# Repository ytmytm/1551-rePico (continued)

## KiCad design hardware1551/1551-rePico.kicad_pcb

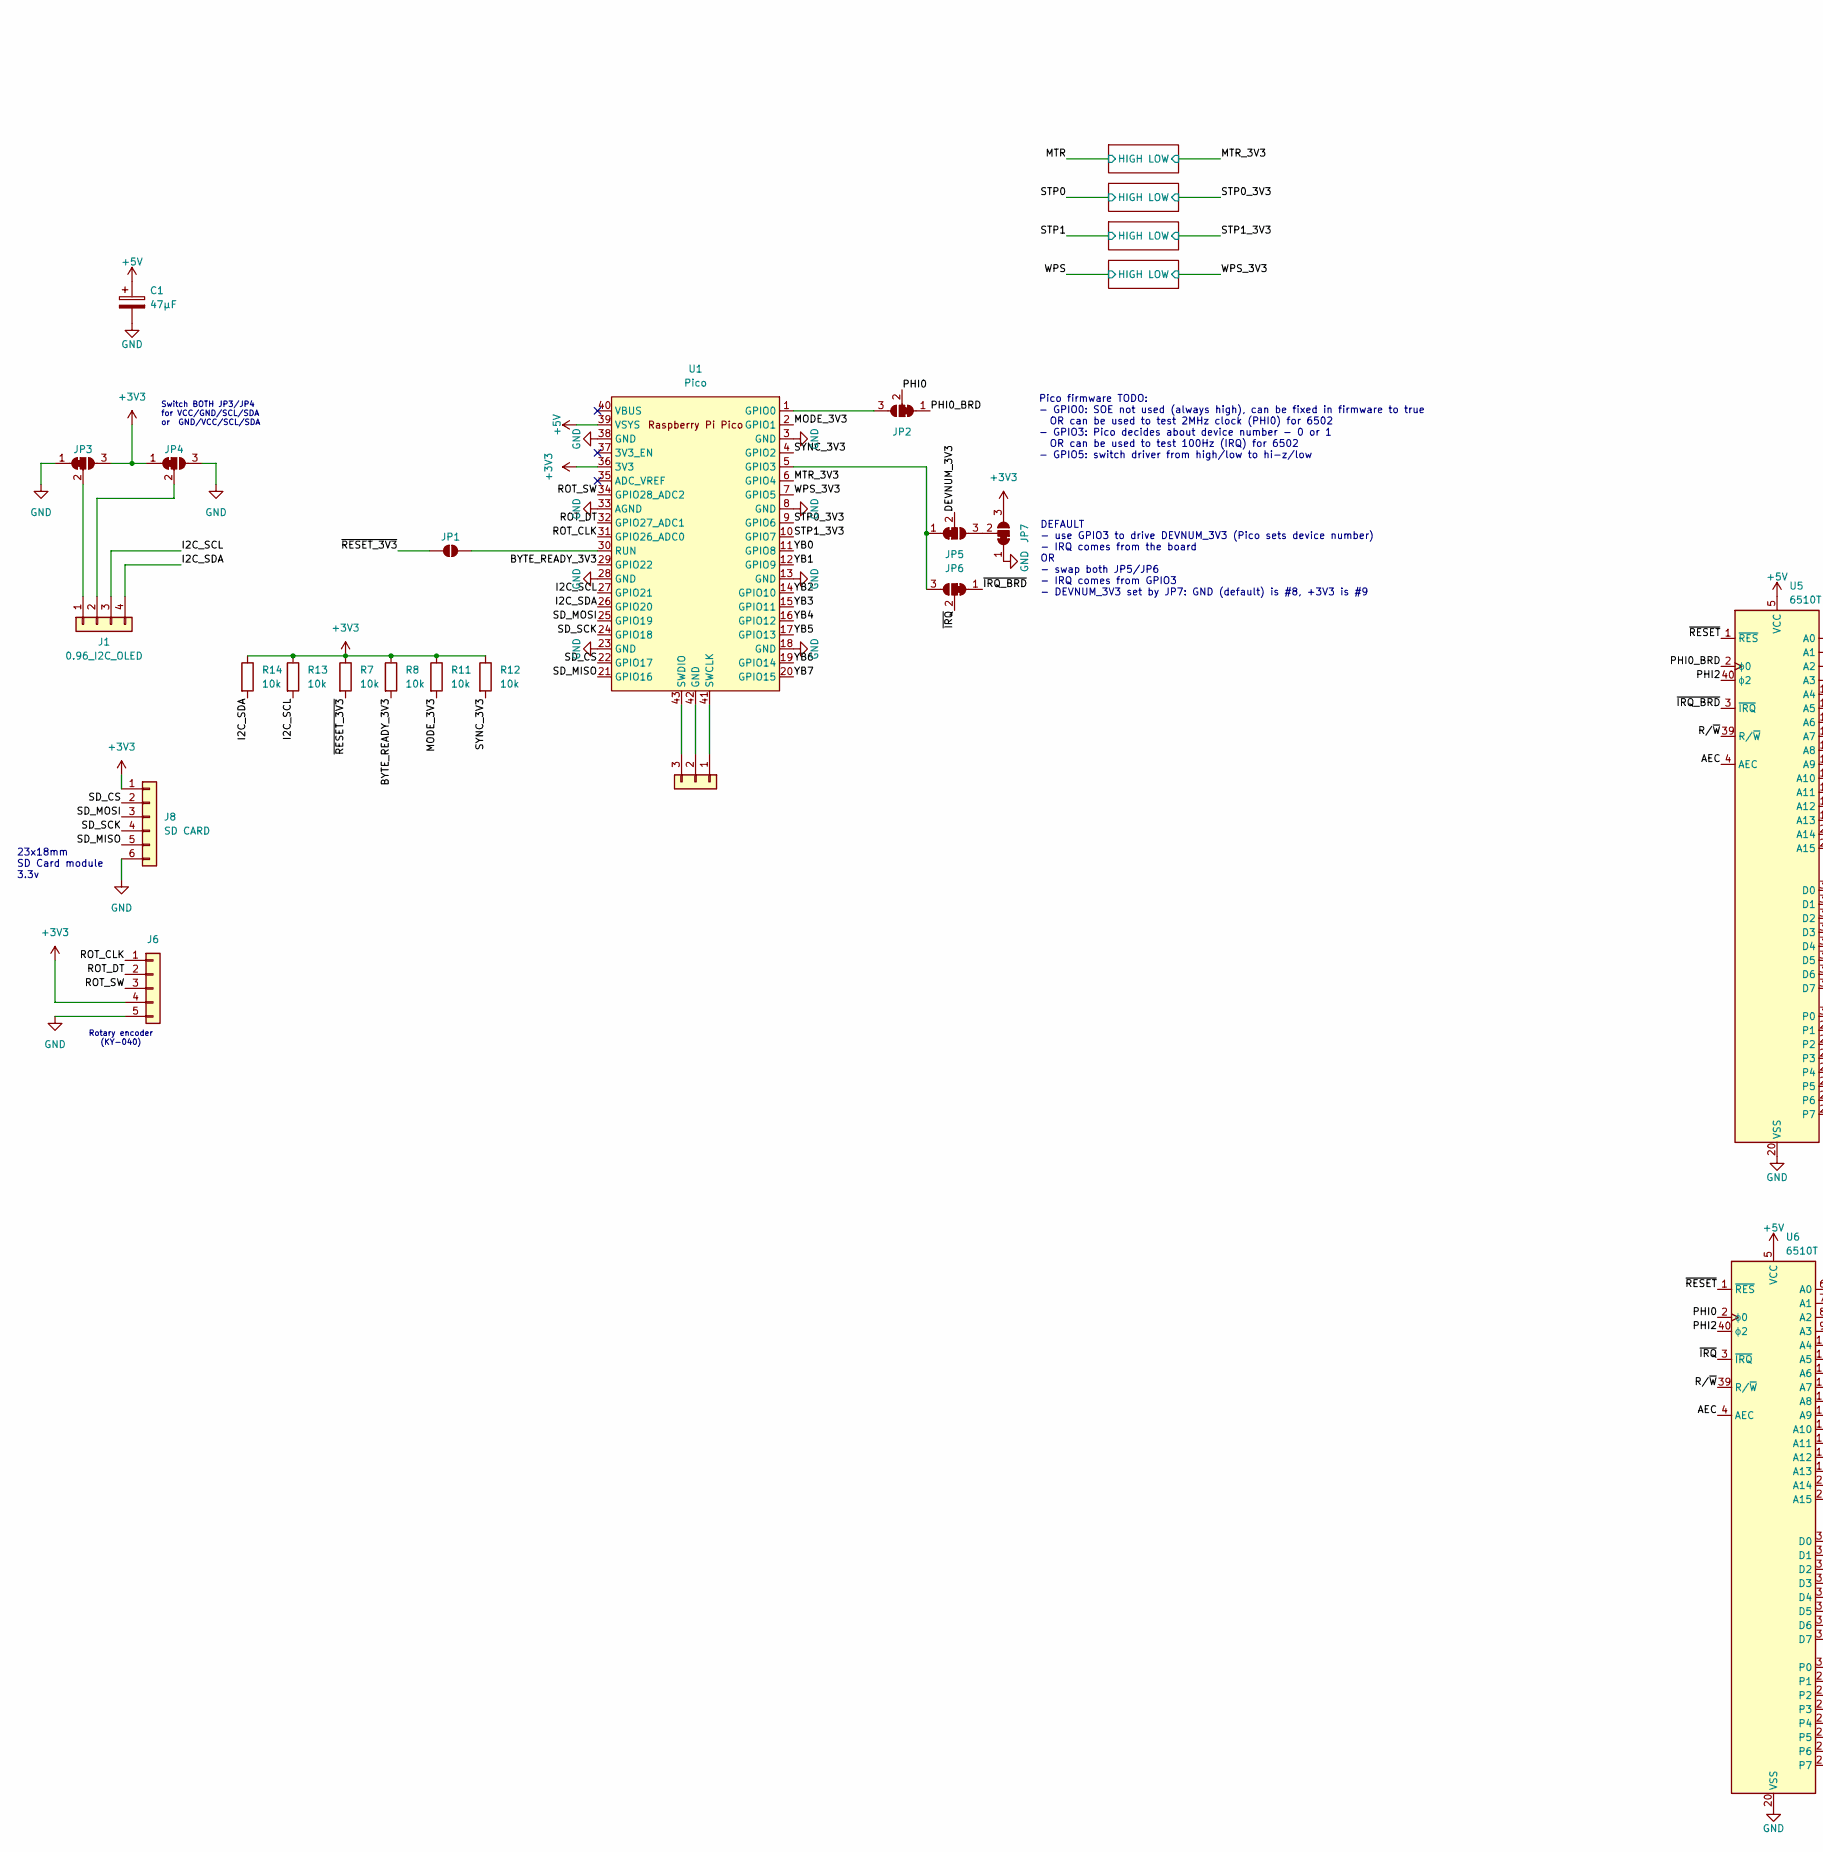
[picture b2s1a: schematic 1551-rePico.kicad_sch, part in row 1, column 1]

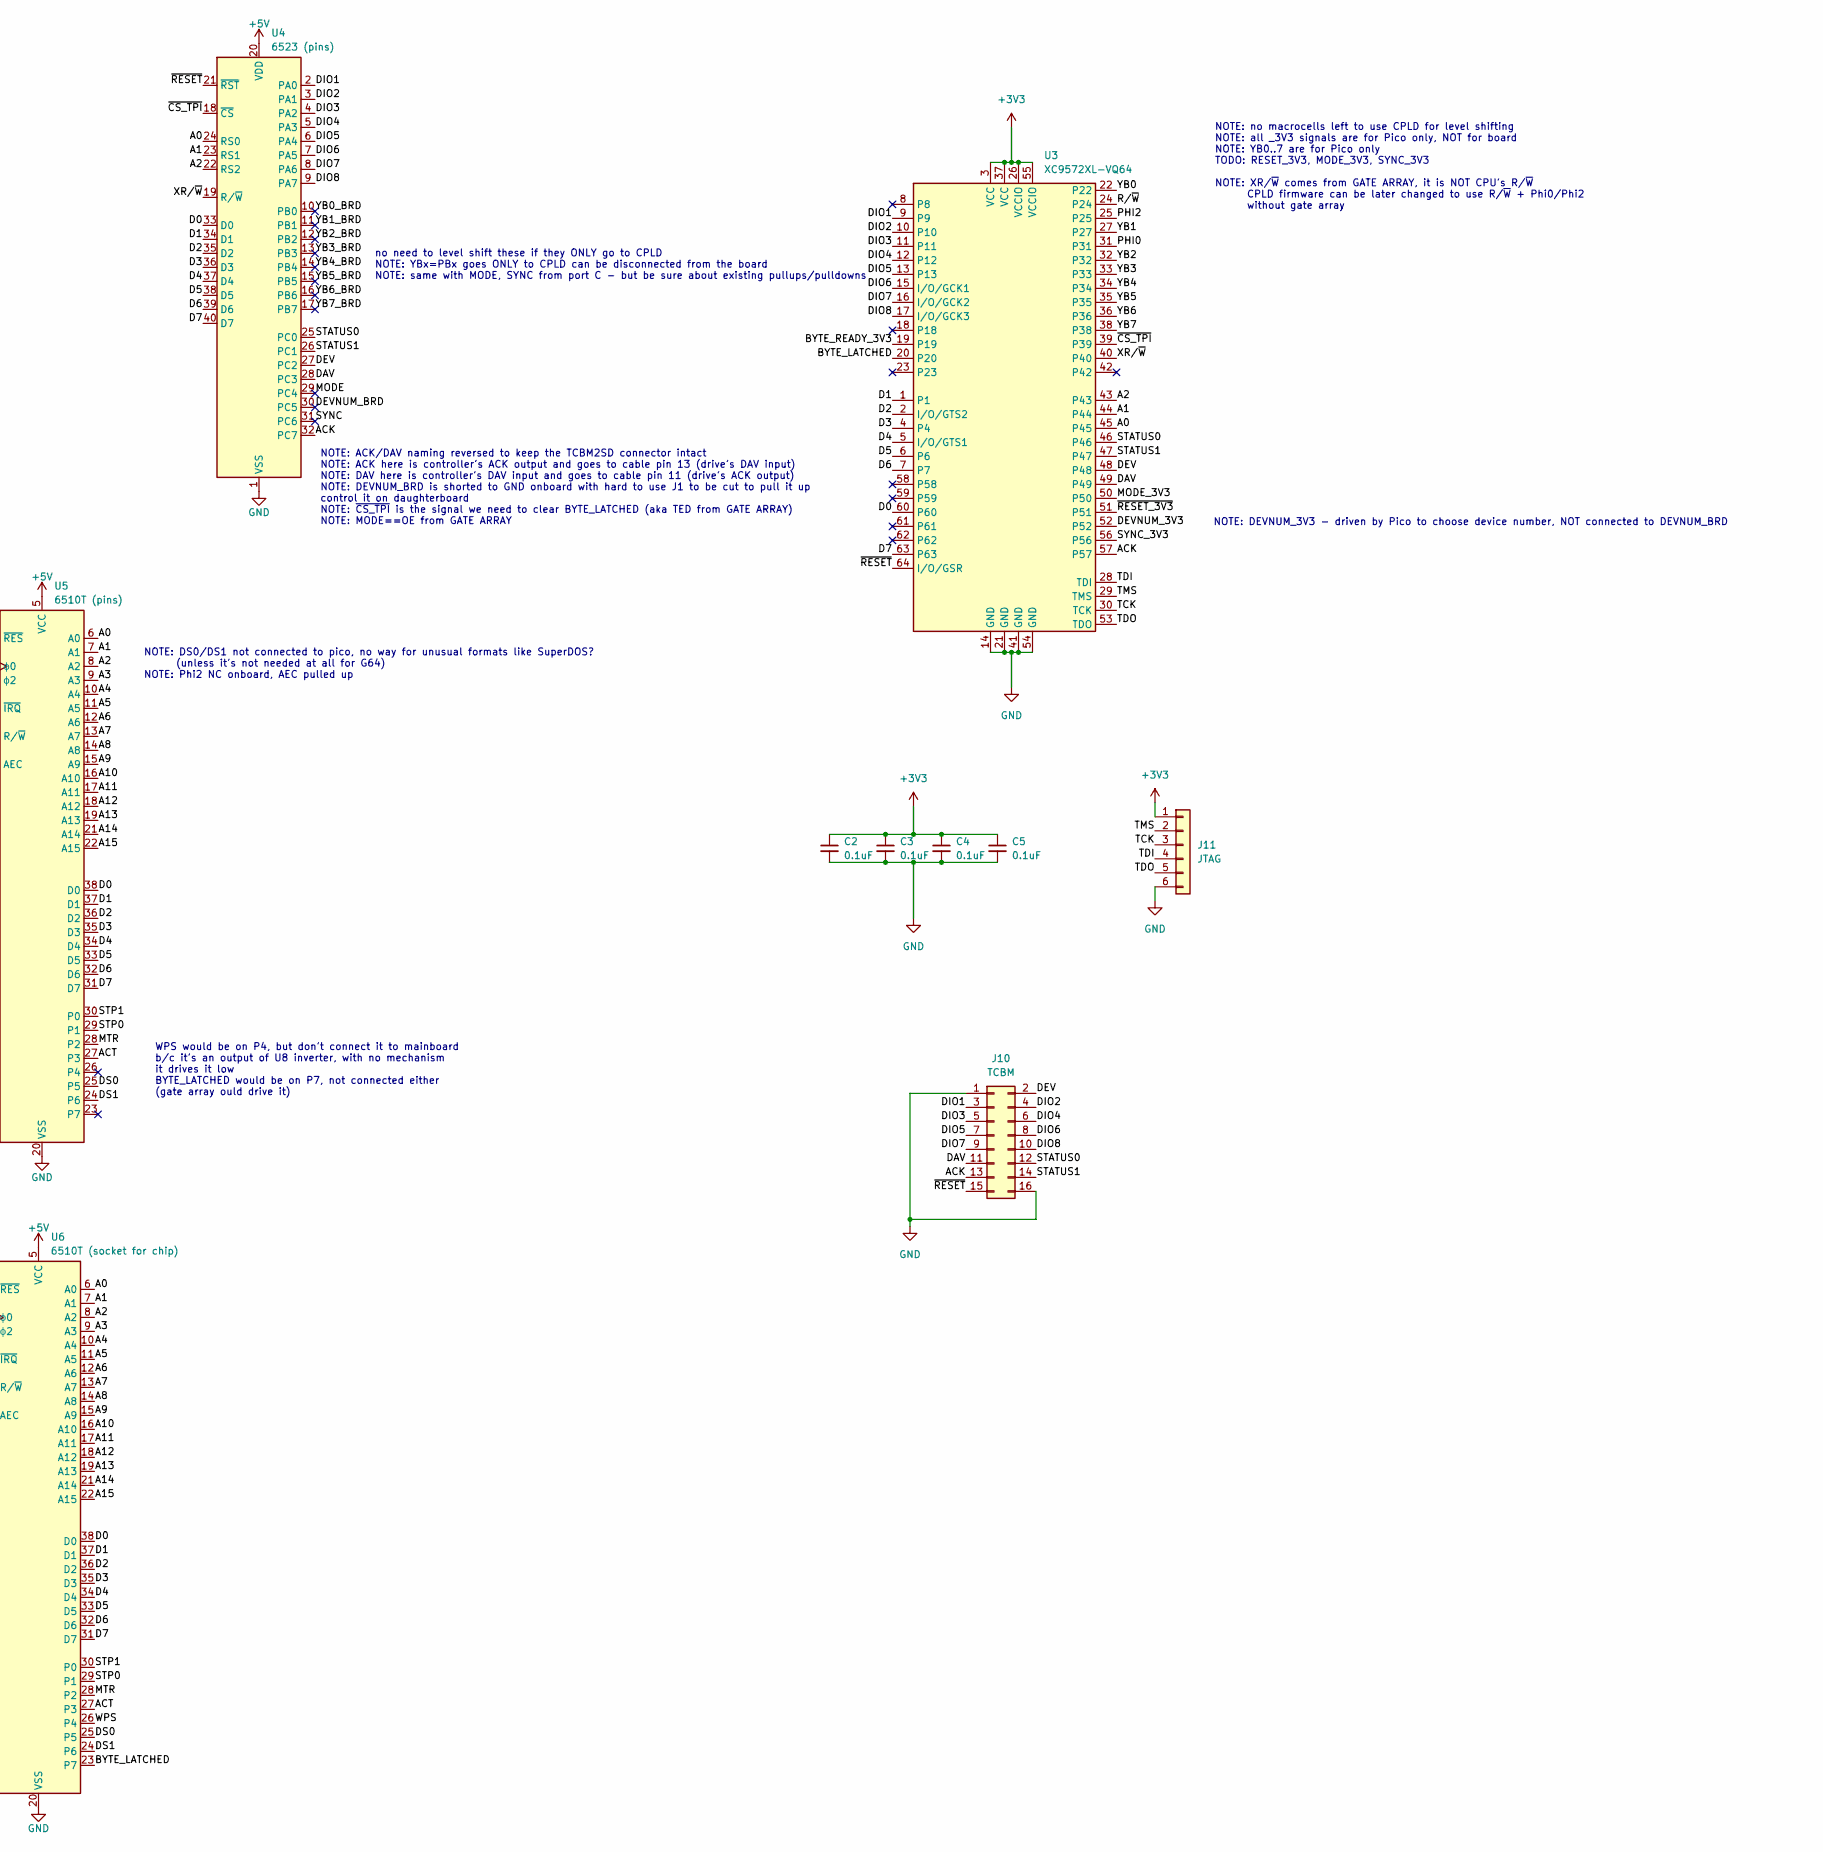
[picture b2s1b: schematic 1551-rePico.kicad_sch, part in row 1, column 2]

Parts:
C1: 47µF; CP_Radial_D5.0mm_P2.50mm
C2, C3, C4, C5: 0.1uF; C_0805_2012Metric_Pad1.18x1.45mm_HandSolder; JLCPCB Part # C49678
J1: 0.96_I2C_OLED; PinHeader_1x04_P2.54mm_Vertical
J6: Conn_01x05; PinHeader_1x05_P2.54mm_Vertical
J8: SD CARD; PinHeader_1x06_P2.54mm_Vertical
J10: TCBM; IDC-Header_2x08_P2.54mm_Vertical
J11: JTAG; PinHeader_1x06_P2.54mm_Vertical
JP1: SolderJumper-2_P1.3mm_Open_RoundedPad1.0x1.5mm
JP2, JP3, JP4, JP5, JP6, JP7: SolderJumper_3_Bridged12; SolderJumper-3_P1.3mm_Bridged12_RoundedPad1.0x1.5mm_NumberL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
R7, R8, R11, R12, R13, R14: 10k; R_0805_2012Metric_Pad1.20x1.40mm_HandSolder; MFR.Part # RCA0510KFLF; JLCPCB Part # C22356686
SWDBG1: DEBUG; PinHeader_1x03_P2.54mm_Vertical
U1: Pico; RPi_Pico_SMD_TH
U3: XC9572XL-VQ64; TQFP-64_10x10mm_P0.5mm; JLCPCB Part # C90569
U4: 6523 (pins); DIP-40_W15.24mm
U5: 6510T (pins); DIP-40_W15.24mm
U6: 6510T (socket for chip); DIP-40_W15.24mm

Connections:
+3V3: C2.1, C3.1, C4.1, C5.1, J6.4, J8.1, J11.1, JP3.3 (B), JP4.1 (A), JP7.3 (B), R7.1, R8.1, R11.1, R12.1, R13.1, R14.1, U1.36 (3V3), U3.3 (VCC), U3.26 (VCCIO), U3.37 (VCC), U3.55 (VCCIO); also elsewhere on the board
+5V: C1.1, U1.39 (VSYS), U4.20 (VDD), U5.5 (VCC), U6.5 (VCC); also elsewhere on the board
/A0: U3.45, U4.24 (RS0), U5.6 (A0), U6.6 (A0)
/A1: U3.44, U4.23 (RS1), U5.7 (A1), U6.7 (A1)
/A2: U3.43, U4.22 (RS2), U5.8 (A2), U6.8 (A2)
/A3: U5.9 (A3), U6.9 (A3)
/A4: U5.10 (A4), U6.10 (A4)
/A5: U5.11 (A5), U6.11 (A5)
/A6: U5.12 (A6), U6.12 (A6)
/A7: U5.13 (A7), U6.13 (A7)
/A8: U5.14 (A8), U6.14 (A8)
/A9: U5.15 (A9), U6.15 (A9)
/A10: U5.16 (A10), U6.16 (A10)
/A11: U5.17 (A11), U6.17 (A11)
/A12: U5.18 (A12), U6.18 (A12)
/A13: U5.19 (A13), U6.19 (A13)
/A14: U5.21 (A14), U6.21 (A14)
/A15: U5.22 (A15), U6.22 (A15)
/ACK: J10.13, U3.57, U4.32 (PC7)
/ACT: U5.27 (P3), U6.27 (P3)
/AEC: U5.4 (AEC), U6.4 (AEC)
/BYTE_LATCHED: U3.20, U6.23 (P7)
/BYTE_READY_3V3: R8.2, U1.29 (GPIO22), U3.19
/D0: U3.60, U4.33 (D0), U5.38 (D0), U6.38 (D0)
/D1: U3.1, U4.34 (D1), U5.37 (D1), U6.37 (D1)
/D2: U3.2 (I/O/GTS2), U4.35 (D2), U5.36 (D2), U6.36 (D2)
/D3: U3.4, U4.36 (D3), U5.35 (D3), U6.35 (D3)
/D4: U3.5 (I/O/GTS1), U4.37 (D4), U5.34 (D4), U6.34 (D4)
/D5: U3.6, U4.38 (D5), U5.33 (D5), U6.33 (D5)
/D6: U3.7, U4.39 (D6), U5.32 (D6), U6.32 (D6)
/D7: U3.63, U4.40 (D7), U5.31 (D7), U6.31 (D7)
/DAV: J10.11, U3.49, U4.28 (PC3)
/DEV: J10.2, U3.48, U4.27 (PC2)
/DEVNUM_3V3: JP5.2 (C), U3.52
/DEVNUM_BRD: U4.30 (PC5)
/DIO1: J10.3, U3.9, U4.2 (PA0)
/DIO2: J10.4, U3.10, U4.3 (PA1)
/DIO3: J10.5, U3.11, U4.4 (PA2)
/DIO4: J10.6, U3.12, U4.5 (PA3)
/DIO5: J10.7, U3.13, U4.6 (PA4)
/DIO6: J10.8, U3.15 (I/O/GCK1), U4.7 (PA5)
/DIO7: J10.9, U3.16 (I/O/GCK2), U4.8 (PA6)
/DIO8: J10.10, U3.17 (I/O/GCK3), U4.9 (PA7)
/DS0: U5.25 (P5), U6.25 (P5)
/DS1: U5.24 (P6), U6.24 (P6)
/I2C_SCL: J1.3, R13.2, U1.27 (GPIO21)
/I2C_SDA: J1.4, R14.2, U1.26 (GPIO20)
/MODE: U4.29 (PC4)
/MODE_3V3: R11.2, U1.2 (GPIO1), U3.50
/MTR: U5.28 (P2), U6.28 (P2); also elsewhere on the board
/MTR_3V3: U1.6 (GPIO4); also elsewhere on the board
/PHI0: JP2.2 (C), U3.31, U6.2 (ϕ0)
/PHI0_BRD: JP2.1 (A), U5.2 (ϕ0)
/PHI2: U3.25, U5.40 (ϕ2), U6.40 (ϕ2)
/ROT_CLK: J6.1, U1.31 (GPIO26_ADC0)
/ROT_DT: J6.2, U1.32 (GPIO27_ADC1)
/ROT_SW: J6.3, U1.34 (GPIO28_ADC2)
/R/~W: U3.24, U5.39 (R/~W), U6.39 (R/~W)
/SD_CS: J8.2, U1.22 (GPIO17)
/SD_MISO: J8.5, U1.21 (GPIO16)
/SD_MOSI: J8.3, U1.25 (GPIO19)
/SD_SCK: J8.4, U1.24 (GPIO18)
/STATUS0: J10.12, U3.46, U4.25 (PC0)
/STATUS1: J10.14, U3.47, U4.26 (PC1)
/STP0: U5.29 (P1), U6.29 (P1); also elsewhere on the board
/STP0_3V3: U1.9 (GPIO6); also elsewhere on the board
/STP1: U5.30 (P0), U6.30 (P0); also elsewhere on the board
/STP1_3V3: U1.10 (GPIO7); also elsewhere on the board
/SYNC: U4.31 (PC6)
/SYNC_3V3: R12.2, U1.4 (GPIO2), U3.56
/TCK: J11.3, U3.30 (TCK)
/TDI: J11.4, U3.28 (TDI)
/TDO: J11.5, U3.53 (TDO)
/TMS: J11.2, U3.29 (TMS)
/WPS: U6.26 (P4); also elsewhere on the board
/WPS_3V3: U1.7 (GPIO5); also elsewhere on the board
/XR/~W: U3.40, U4.19 (R/~W)
/YB0: U1.11 (GPIO8), U3.22
/YB0_BRD: U4.10 (PB0)
/YB1: U1.12 (GPIO9), U3.27
/YB1_BRD: U4.11 (PB1)
/YB2: U1.14 (GPIO10), U3.32
/YB2_BRD: U4.12 (PB2)
/YB3: U1.15 (GPIO11), U3.33
/YB3_BRD: U4.13 (PB3)
/YB4: U1.16 (GPIO12), U3.34
/YB4_BRD: U4.14 (PB4)
/YB5: U1.17 (GPIO13), U3.35
/YB5_BRD: U4.15 (PB5)
/YB6: U1.19 (GPIO14), U3.36
/YB6_BRD: U4.16 (PB6)
/YB7: U1.20 (GPIO15), U3.38
/YB7_BRD: U4.17 (PB7)
/~CS_TPI: U3.39, U4.18 (~CS)
/~IRQ_BRD: JP6.1 (A), U5.3 (~IRQ)
/~IRQ: JP6.2 (C), U6.3 (~IRQ)
/~RESET_3V3: JP1.1 (A), R7.2, U3.51
/~RESET: J10.15, U3.64 (I/O/GSR), U4.21 (~RST), U5.1 (~RES), U6.1 (~RES)
GND: C1.2, C2.2, C3.2, C4.2, C5.2, J6.5, J8.6, J10.1, J10.16, J11.6, JP3.1 (A), JP4.3 (B), JP7.1 (A), U1.3 (GND), U1.8 (GND), U1.13 (GND), U1.18 (GND), U1.23 (GND), U1.28 (GND), U1.33 (AGND), U1.38 (GND), U3.14 (GND), U3.21 (GND), U3.41 (GND), U3.54 (GND), U4.1 (VSS), U5.20 (VSS), U6.20 (VSS)
unnamed: J1.1, JP3.2 (C)
unnamed: J1.2, JP4.2 (C)
unnamed: JP1.2 (B), U1.30 (RUN)
unnamed: JP2.3 (B), U1.1 (GPIO0)
unnamed: JP5.1 (A), JP6.3 (B), U1.5 (GPIO3)
unnamed: JP5.3 (B), JP7.2 (C)
unnamed: SWDBG1.1, U1.41 (SWCLK)
unnamed: SWDBG1.2, U1.42 (GND)
unnamed: SWDBG1.3, U1.43 (SWDIO)

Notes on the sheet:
DEFAULT - use GPIO3 to drive DEVNUM_3V3 (Pico sets device number) - IRQ comes from the board OR - swap both JP5/JP6 - IRQ comes from GPIO3 - DEVNUM_3V3 set by JP7: GND (default) is #8, +3V3 is #9
Rotary encoder (KY-040)
NOTE: DS0/DS1 not connected to pico, no way for unusual formats like SuperDOS? (unless it's not needed at all for G64) NOTE: Phi2 NC onboard, AEC pulled up
NOTE: DEVNUM_3V3 - driven by Pico to choose device number, NOT connected to DEVNUM_BRD
NOTE: no macrocells left to use CPLD for level shifting NOTE: all _3V3 signals are for Pico only, NOT for board NOTE: YB0..7 are for Pico only TODO: RESET_3V3, MODE_3V3, SYNC_3V3 NOTE: XR/~{W} comes from GATE ARRAY, it is NOT CPU's R/~{W} CPLD firmware can be later changed to use R/~{W} + Phi0/Phi2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
NOTE: ACK/DAV naming reversed to keep the TCBM2SD connector intact NOTE: ACK here is controller's ACK output and goes to cable pin 13 (drive's DAV input) NOTE: DAV here is controller's DAV input and goes to cable pin 11 (drive's ACK output) NOTE: DEVNUM_BRD is shorted to GND onboard with hard to us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
23x18mm SD Card module 3.3v
no need to level shift these if they ONLY go to CPLD NOTE: YBx=PBx goes ONLY to CPLD can be disconnected from the board NOTE: same with MODE, SYNC from port C - but be sure about existing pullups/pulldowns
Switch BOTH JP3/JP4 for VCC/GND/SCL/SDA or GND/VCC/SCL/SDA
WPS would be on P4, but don't connect it to mainboard b/c it's an output of U8 inverter, with no mechanism it drives it low BYTE_LATCHED would be on P7, not connected either (gate array ould drive it)
Pico firmware TODO: - GPIO0: SOE not used (always high), can be fixed in firmware to true OR can be used to test 2MHz clock (PHI0) for 6502 - GPIO3: Pico decides about device number - 0 or 1 OR can be used to test 100Hz (IRQ) for 6502 - GPIO5: switch driver from high/low to hi-z/low

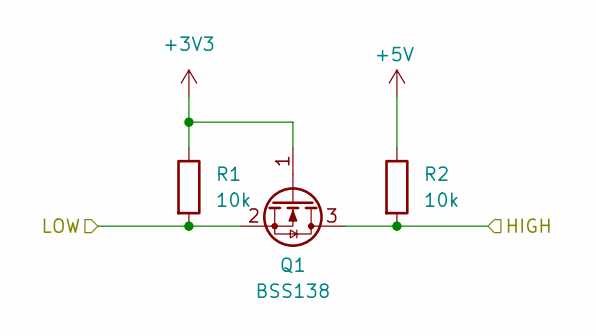
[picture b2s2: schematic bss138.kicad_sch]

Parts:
Q1: BSS138; SOT-23; MFR.Part # BSS138; JLCPCB Part # C78284
R1, R2: 10k; R_0805_2012Metric_Pad1.20x1.40mm_HandSolder; MFR.Part # RCA0510KFLF; JLCPCB Part # C22356686

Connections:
+3V3: Q1.1 (G), R1.1; also elsewhere on the board
+5V: R2.1; also elsewhere on the board
/MTR: Q1.3 (D), R2.2; also elsewhere on the board
/MTR_3V3: Q1.2 (S), R1.2; also elsewhere on the board

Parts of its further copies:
Q2, Q3, Q4: BSS138; SOT-23; MFR.Part # BSS138; JLCPCB Part # C78284
R3, R4, R5, R6, R9, R10: 10k; R_0805_2012Metric_Pad1.20x1.40mm_HandSolder; MFR.Part # RCA0510KFLF; JLCPCB Part # C22356686

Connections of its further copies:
+3V3: Q2.1 (G), Q3.1 (G), Q4.1 (G), R3.1, R5.1, R9.1; also elsewhere on the board
+5V: R4.1, R6.1, R10.1; also elsewhere on the board
/STP0: Q2.3 (D), R4.2; also elsewhere on the board
/STP0_3V3: Q2.2 (S), R3.2; also elsewhere on the board
/STP1: Q3.3 (D), R6.2; also elsewhere on the board
/STP1_3V3: Q3.2 (S), R5.2; also elsewhere on the board
/WPS: Q4.3 (D), R10.2; also elsewhere on the board
/WPS_3V3: Q4.2 (S), R9.2; also elsewhere on the board

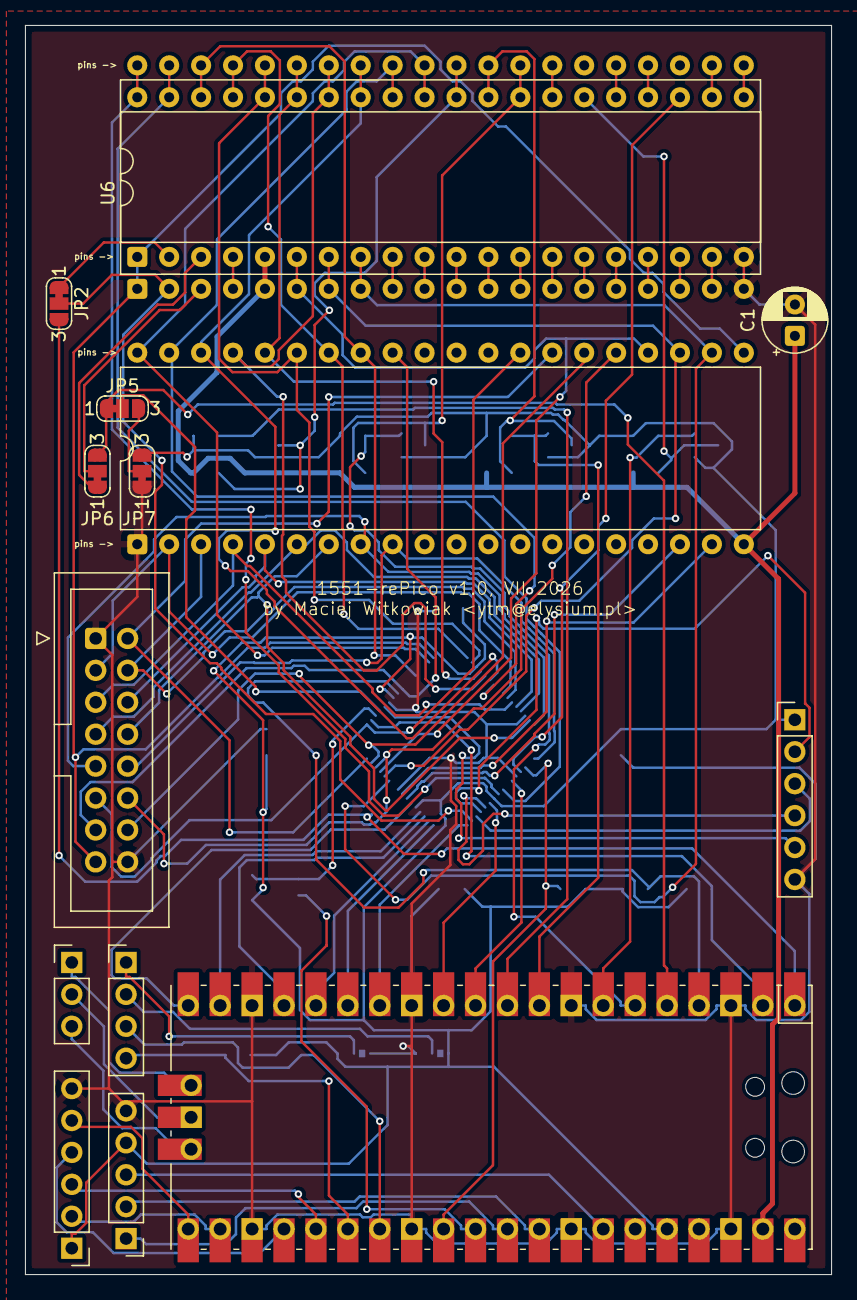
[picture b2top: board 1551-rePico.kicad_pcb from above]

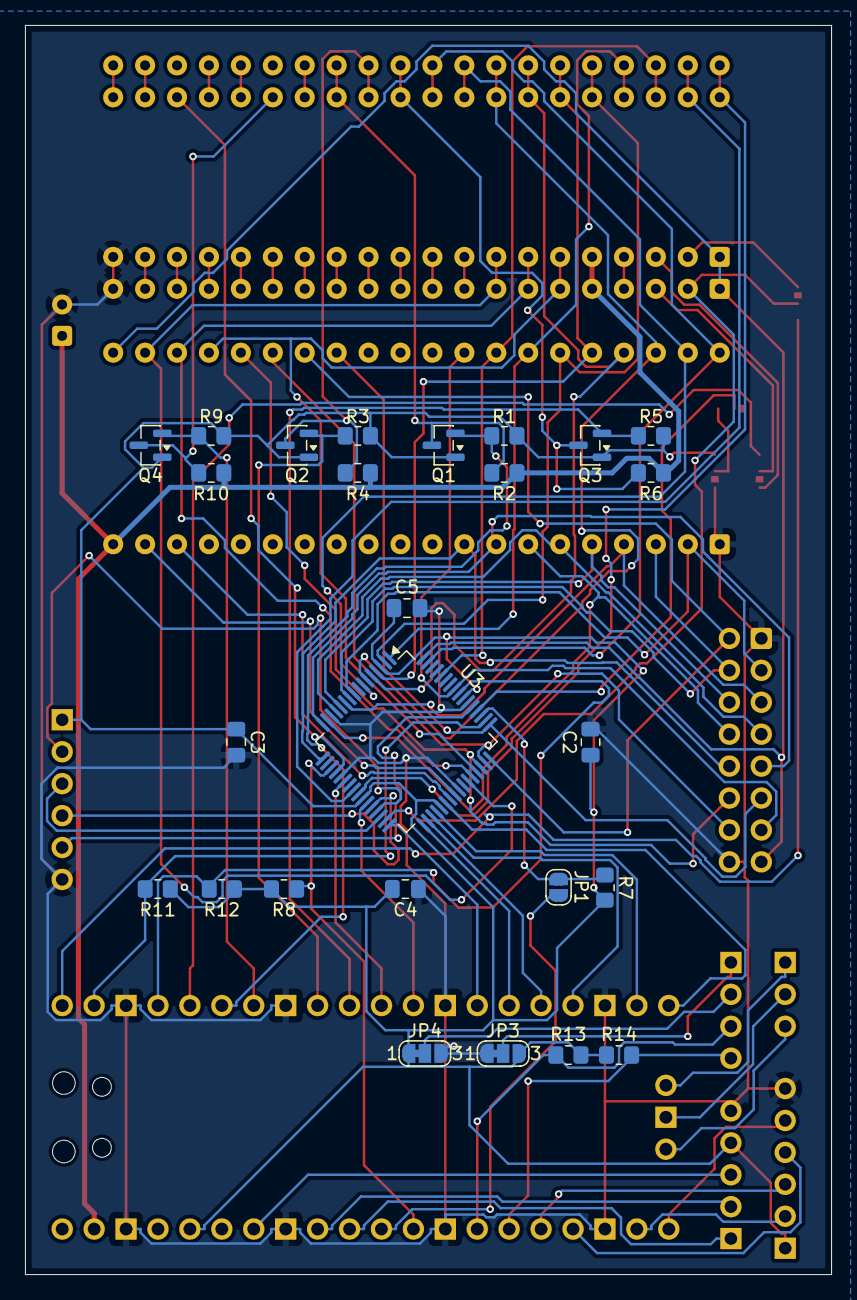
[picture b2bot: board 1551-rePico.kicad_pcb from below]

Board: 2 copper layers, 64.1 x 99.4 mm, 41 parts (26 on the bottom side), 97 nets.

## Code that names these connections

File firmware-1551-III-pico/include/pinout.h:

/**********************************
 * header - pinout assignment for Pico2 to baseboard
 *
 * Author: F00K42
 * Last change: 2026/02/15
***********************************/
#include "hardware/spi.h"

// Gate-array / 1551 bus connection (GPIO numbers shared across targets)
// 1551: GPIO0=PHI0(PWM), GPIO1=MODE, GPIO3=DEVNUM(static) or IRQ PWM (see board1551.h), GPIO8..15=YB0..7
#define GPIO_SOE    0
#define GPIO_OE     1
#define GPIO_SYNC   2
#define GPIO_SOE_GA 3
#define GPIO_MTR    4
#define GPIO_WPS    5
#define GPIO_STP0   6
#define GPIO_STP1   7

#define GPIO_PAPORT 8  //defines the first bit of 8
#define PAPORT_MASK (uint32_t)(0xFF<<GPIO_PAPORT)
/*
#define GPIO_PA0    8
#define GPIO_PA1    9
#define GPIO_PA2    10
#define GPIO_PA3    11
#define GPIO_PA4    12
#define GPIO_PA5    13
#define GPIO_PA6    14
#define GPIO_PA7    15
*/

// SPI defines
#define SPI_PORT    spi0
#define SPI_MISO    16
#define SPI_CS      17
#define SPI_SCK     18
#define SPI_MOSI    19

// I2C defines
#define I2C_PORT    i2c0
#define I2C_SDA     20
#define I2C_SCL     21

// Pi1551-III front panel via 74HCT165 (JP1..JP3 bridged 1-2)
#define GPIO_SERIAL_LOAD  26  // /PL
#define GPIO_SERIAL_CLK   27  // CP
#define GPIO_SERIAL_DT    28  // Q7

#define GPIO_BRDY   22

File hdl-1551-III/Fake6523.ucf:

NET "_reset"  LOC = "P64"  ;    // RESET // TCBM bus
NET "data<0>"  LOC = "P60" ;
NET "data<1>"  LOC = "P1"  ;
NET "data<2>"  LOC = "P2"  ;
NET "data<3>"  LOC = "P4"  ;
NET "data<4>"  LOC = "P5"  ;
NET "data<5>"  LOC = "P6"  ;
NET "data<6>"  LOC = "P7"  ;
NET "data<7>"  LOC = "P63"  ;
NET "port_a<0>"  LOC = "P9"  ;  // DIO1 // TCBM bus
NET "port_a<1>"  LOC = "P10"  ; // DIO2
NET "port_a<2>"  LOC = "P11"  ; // DIO3
NET "port_a<3>"  LOC = "P12"  ; // DIO4
NET "port_a<4>"  LOC = "P13"  ; // DIO5
NET "port_a<5>"  LOC = "P15"  ; // DIO6
NET "port_a<6>"  LOC = "P16"  ; // DIO7
NET "port_a<7>"  LOC = "P17"  ; // DIO8
NET "port_b<0>"  LOC = "P22"  ; // YB0  // head register
NET "port_b<1>"  LOC = "P27"  ; // YB1
NET "port_b<2>"  LOC = "P32"  ; // YB2
NET "port_b<3>"  LOC = "P33"  ; // YB3
NET "port_b<4>"  LOC = "P34"  ; // YB4
NET "port_b<5>"  LOC = "P35"  ; // YB5
NET "port_b<6>"  LOC = "P36"  ; // YB6
NET "port_b<7>"  LOC = "P38"  ; // YB7
NET "port_c<0>"  LOC = "P46"  ; // STATUS0
NET "port_c<1>"  LOC = "P47"  ; // STATUS1
NET "port_c<2>"  LOC = "P48"  ; // DEV
NET "port_c<3>"  LOC = "P49"  ; // DAV
NET "port_c<4>"  LOC = "P50"  ; // MODE (head R/W)
NET "port_c<5>"  LOC = "P52"  ; // DEVNUM (0=#9, 1=#8)
NET "port_c<6>"  LOC = "P56"  ; // SYNC
NET "port_c<7>"  LOC = "P57"  ; // ACK
NET "rs<0>"  LOC = "P45"  ;     // A0
NET "rs<1>"  LOC = "P44"  ;     // A1
NET "rs<2>"  LOC = "P43"  ;     // A2

NET "byte_ready_3v3" LOC = "P19";
NET "byte_latched" LOC = "P20";

NET "a13"  LOC = "P61"  ;       // CPU A13
NET "a14"  LOC = "P39"  ;       // CPU A14; replaces external TPI /CS input
NET "a15"  LOC = "P62"  ;       // CPU A15

NET "_ramsel" LOC = "P58";      // /RAMSEL (TEMP: address decode OR ~PHI2)
NET "_ramoe" LOC = "P42";       // /RAMOE (follows /RAMSEL)
NET "_romsel" LOC = "P59";      // /ROMSEL (TEMP: address decode AND PHI2)

NET "_writereal" LOC = "P24";   // R/W from CPU
//NET "phi0" LOC = "P31";
NET "phi2" LOC = "P25";         // PHI2 from CPU
NET "_xrw" LOC = "P40";         // output to RAM
